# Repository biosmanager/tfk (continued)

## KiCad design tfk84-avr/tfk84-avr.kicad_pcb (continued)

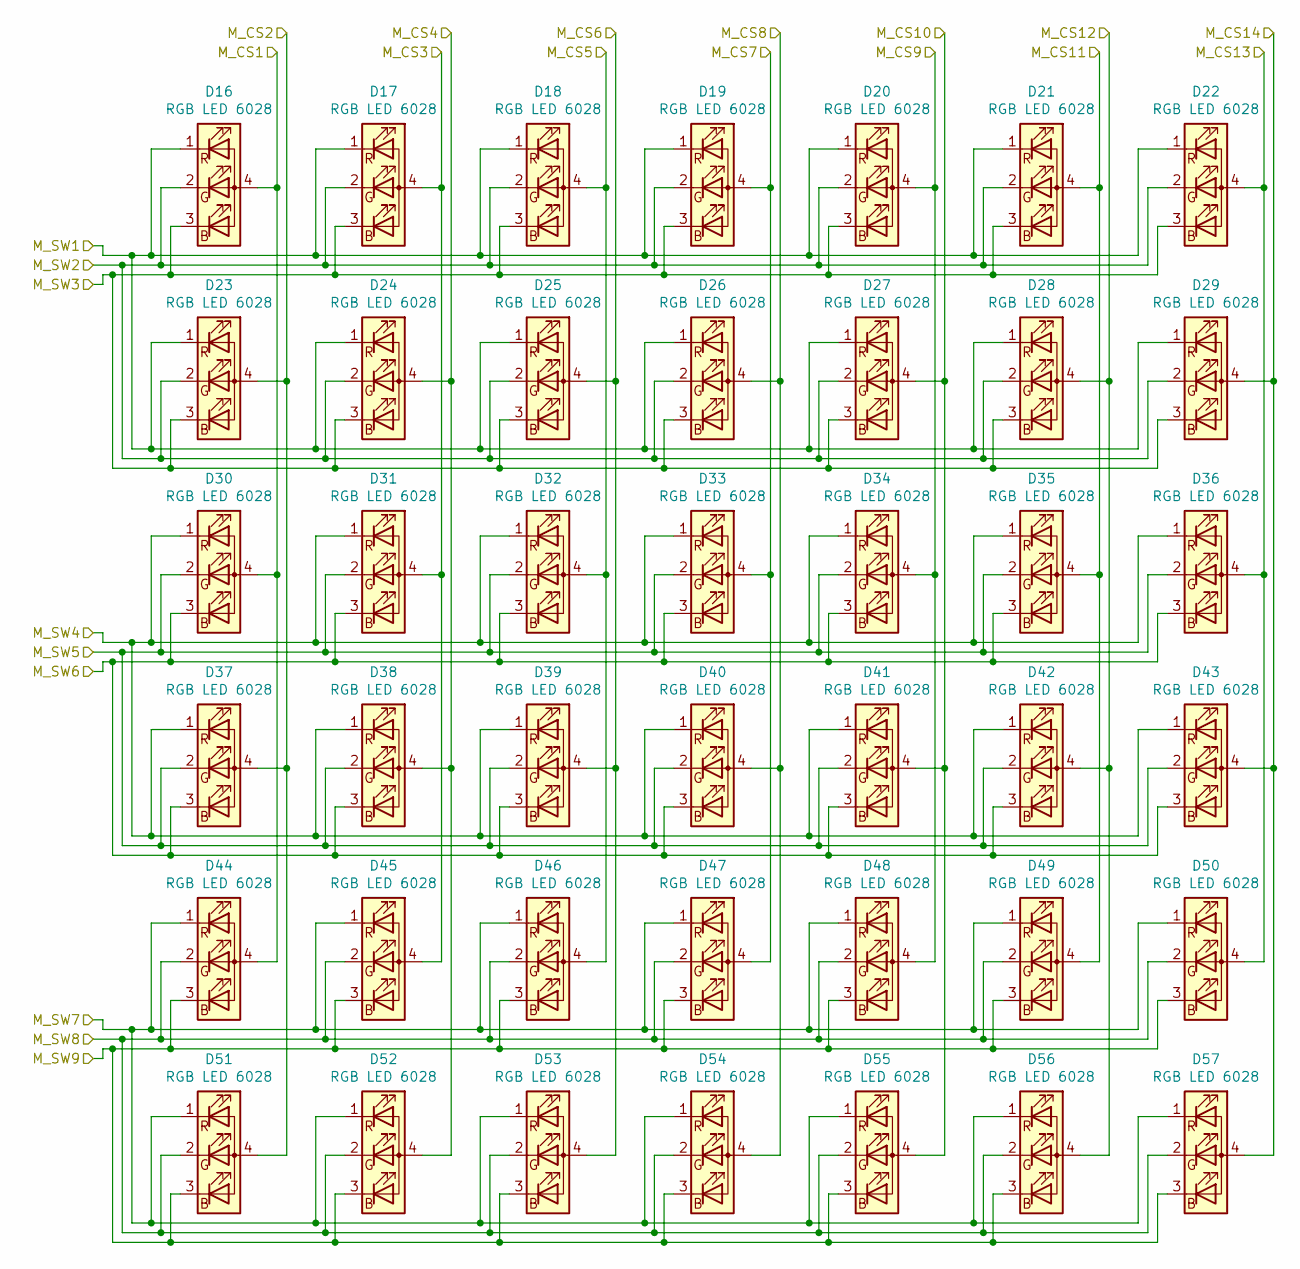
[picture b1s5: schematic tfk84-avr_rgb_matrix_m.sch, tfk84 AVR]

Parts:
D16, D17, D18, D19, D20, D21, D22, D23, D24, D25, D26, D27, D28, D29, D30, D31, D32, D33, D34, D35, D36, D37, D38, D39, D40, D41, D42, D43, D44, D45, D46, D47, D48, D49, D50, D51, D52, D53, D54, D55, D56, D57: RGB LED 6028; RGB-6028

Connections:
/tfk84 RGB Matrix/tfk84 AVR RGB Matrix Master/M_CS1: D16.4 (A), D30.4 (A), D44.4 (A); also elsewhere on the board
/tfk84 RGB Matrix/tfk84 AVR RGB Matrix Master/M_CS2: D23.4 (A), D37.4 (A), D51.4 (A); also elsewhere on the board
/tfk84 RGB Matrix/tfk84 AVR RGB Matrix Master/M_CS3: D17.4 (A), D31.4 (A), D45.4 (A); also elsewhere on the board
/tfk84 RGB Matrix/tfk84 AVR RGB Matrix Master/M_CS4: D24.4 (A), D38.4 (A), D52.4 (A); also elsewhere on the board
/tfk84 RGB Matrix/tfk84 AVR RGB Matrix Master/M_CS5: D18.4 (A), D32.4 (A), D46.4 (A); also elsewhere on the board
/tfk84 RGB Matrix/tfk84 AVR RGB Matrix Master/M_CS6: D25.4 (A), D39.4 (A), D53.4 (A); also elsewhere on the board
/tfk84 RGB Matrix/tfk84 AVR RGB Matrix Master/M_CS7: D19.4 (A), D33.4 (A), D47.4 (A); also elsewhere on the board
/tfk84 RGB Matrix/tfk84 AVR RGB Matrix Master/M_CS8: D26.4 (A), D40.4 (A), D54.4 (A); also elsewhere on the board
/tfk84 RGB Matrix/tfk84 AVR RGB Matrix Master/M_CS9: D20.4 (A), D34.4 (A), D48.4 (A); also elsewhere on the board
/tfk84 RGB Matrix/tfk84 AVR RGB Matrix Master/M_CS10: D27.4 (A), D41.4 (A), D55.4 (A); also elsewhere on the board
/tfk84 RGB Matrix/tfk84 AVR RGB Matrix Master/M_CS11: D21.4 (A), D35.4 (A), D49.4 (A); also elsewhere on the board
/tfk84 RGB Matrix/tfk84 AVR RGB Matrix Master/M_CS12: D28.4 (A), D42.4 (A), D56.4 (A); also elsewhere on the board
/tfk84 RGB Matrix/tfk84 AVR RGB Matrix Master/M_CS13: D22.4 (A), D36.4 (A), D50.4 (A); also elsewhere on the board
/tfk84 RGB Matrix/tfk84 AVR RGB Matrix Master/M_CS14: D29.4 (A), D43.4 (A), D57.4 (A); also elsewhere on the board
/tfk84 RGB Matrix/tfk84 AVR RGB Matrix Master/M_SW1: D16.1 (RK), D17.1 (RK), D18.1 (RK), D19.1 (RK), D20.1 (RK), D21.1 (RK), D22.1 (RK), D23.1 (RK), D24.1 (RK), D25.1 (RK), D26.1 (RK), D27.1 (RK), D28.1 (RK), D29.1 (RK); also elsewhere on the board
/tfk84 RGB Matrix/tfk84 AVR RGB Matrix Master/M_SW2: D16.2 (GK), D17.2 (GK), D18.2 (GK), D19.2 (GK), D20.2 (GK), D21.2 (GK), D22.2 (GK), D23.2 (GK), D24.2 (GK), D25.2 (GK), D26.2 (GK), D27.2 (GK), D28.2 (GK), D29.2 (GK); also elsewhere on the board
/tfk84 RGB Matrix/tfk84 AVR RGB Matrix Master/M_SW3: D16.3 (BK), D17.3 (BK), D18.3 (BK), D19.3 (BK), D20.3 (BK), D21.3 (BK), D22.3 (BK), D23.3 (BK), D24.3 (BK), D25.3 (BK), D26.3 (BK), D27.3 (BK), D28.3 (BK), D29.3 (BK); also elsewhere on the board
/tfk84 RGB Matrix/tfk84 AVR RGB Matrix Master/M_SW4: D30.1 (RK), D31.1 (RK), D32.1 (RK), D33.1 (RK), D34.1 (RK), D35.1 (RK), D36.1 (RK), D37.1 (RK), D38.1 (RK), D39.1 (RK), D40.1 (RK), D41.1 (RK), D42.1 (RK), D43.1 (RK); also elsewhere on the board
/tfk84 RGB Matrix/tfk84 AVR RGB Matrix Master/M_SW5: D30.2 (GK), D31.2 (GK), D32.2 (GK), D33.2 (GK), D34.2 (GK), D35.2 (GK), D36.2 (GK), D37.2 (GK), D38.2 (GK), D39.2 (GK), D40.2 (GK), D41.2 (GK), D42.2 (GK), D43.2 (GK); also elsewhere on the board
/tfk84 RGB Matrix/tfk84 AVR RGB Matrix Master/M_SW6: D30.3 (BK), D31.3 (BK), D32.3 (BK), D33.3 (BK), D34.3 (BK), D35.3 (BK), D36.3 (BK), D37.3 (BK), D38.3 (BK), D39.3 (BK), D40.3 (BK), D41.3 (BK), D42.3 (BK), D43.3 (BK); also elsewhere on the board
/tfk84 RGB Matrix/tfk84 AVR RGB Matrix Master/M_SW7: D44.1 (RK), D45.1 (RK), D46.1 (RK), D47.1 (RK), D48.1 (RK), D49.1 (RK), D50.1 (RK), D51.1 (RK), D52.1 (RK), D53.1 (RK), D54.1 (RK), D55.1 (RK), D56.1 (RK), D57.1 (RK); also elsewhere on the board
/tfk84 RGB Matrix/tfk84 AVR RGB Matrix Master/M_SW8: D44.2 (GK), D45.2 (GK), D46.2 (GK), D47.2 (GK), D48.2 (GK), D49.2 (GK), D50.2 (GK), D51.2 (GK), D52.2 (GK), D53.2 (GK), D54.2 (GK), D55.2 (GK), D56.2 (GK), D57.2 (GK); also elsewhere on the board
/tfk84 RGB Matrix/tfk84 AVR RGB Matrix Master/M_SW9: D44.3 (BK), D45.3 (BK), D46.3 (BK), D47.3 (BK), D48.3 (BK), D49.3 (BK), D50.3 (BK), D51.3 (BK), D52.3 (BK), D53.3 (BK), D54.3 (BK), D55.3 (BK), D56.3 (BK), D57.3 (BK); also elsewhere on the board

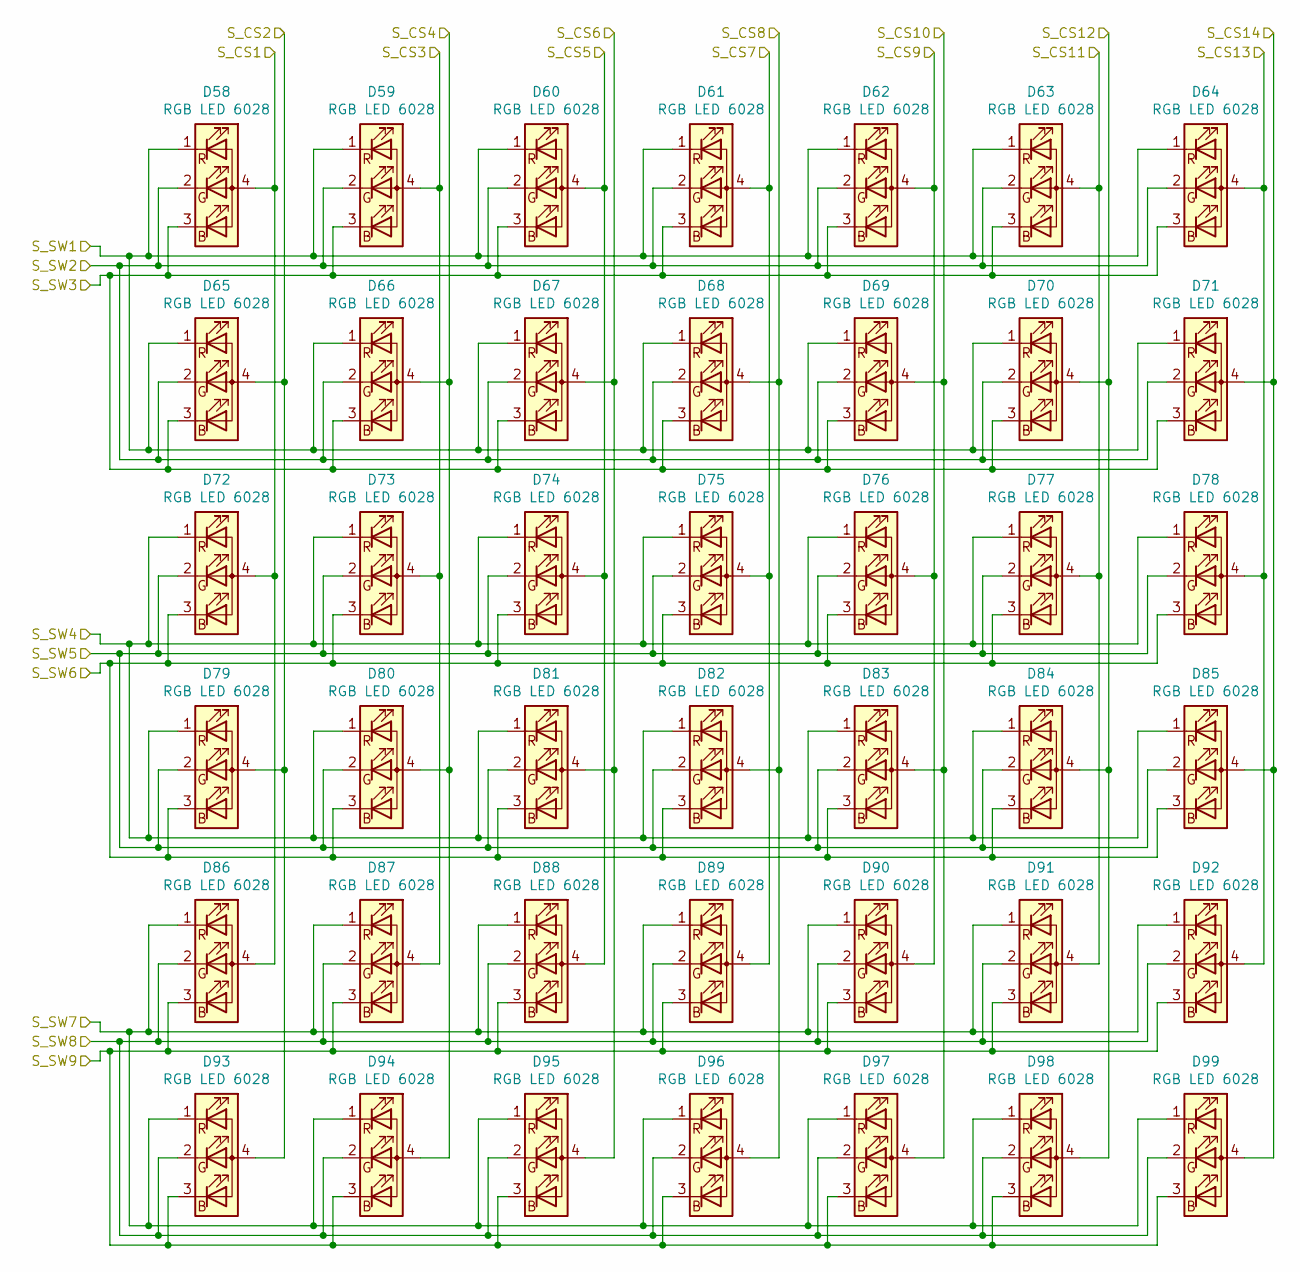
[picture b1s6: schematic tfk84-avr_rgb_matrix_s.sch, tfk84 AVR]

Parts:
D58, D59, D60, D61, D62, D63, D64, D65, D66, D67, D68, D69, D70, D71, D72, D73, D74, D75, D76, D77, D78, D79, D80, D81, D82, D83, D84, D85, D86, D87, D88, D89, D90, D91, D92, D93, D94, D95, D96, D97, D98, D99: RGB LED 6028; RGB-6028

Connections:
/tfk84 RGB Matrix/tfk84 AVR RGB Matrix Slave/S_CS1: D58.4 (A), D72.4 (A), D86.4 (A); also elsewhere on the board
/tfk84 RGB Matrix/tfk84 AVR RGB Matrix Slave/S_CS2: D65.4 (A), D79.4 (A), D93.4 (A); also elsewhere on the board
/tfk84 RGB Matrix/tfk84 AVR RGB Matrix Slave/S_CS3: D59.4 (A), D73.4 (A), D87.4 (A); also elsewhere on the board
/tfk84 RGB Matrix/tfk84 AVR RGB Matrix Slave/S_CS4: D66.4 (A), D80.4 (A), D94.4 (A); also elsewhere on the board
/tfk84 RGB Matrix/tfk84 AVR RGB Matrix Slave/S_CS5: D60.4 (A), D74.4 (A), D88.4 (A); also elsewhere on the board
/tfk84 RGB Matrix/tfk84 AVR RGB Matrix Slave/S_CS6: D67.4 (A), D81.4 (A), D95.4 (A); also elsewhere on the board
/tfk84 RGB Matrix/tfk84 AVR RGB Matrix Slave/S_CS7: D61.4 (A), D75.4 (A), D89.4 (A); also elsewhere on the board
/tfk84 RGB Matrix/tfk84 AVR RGB Matrix Slave/S_CS8: D68.4 (A), D82.4 (A), D96.4 (A); also elsewhere on the board
/tfk84 RGB Matrix/tfk84 AVR RGB Matrix Slave/S_CS9: D62.4 (A), D76.4 (A), D90.4 (A); also elsewhere on the board
/tfk84 RGB Matrix/tfk84 AVR RGB Matrix Slave/S_CS10: D69.4 (A), D83.4 (A), D97.4 (A); also elsewhere on the board
/tfk84 RGB Matrix/tfk84 AVR RGB Matrix Slave/S_CS11: D63.4 (A), D77.4 (A), D91.4 (A); also elsewhere on the board
/tfk84 RGB Matrix/tfk84 AVR RGB Matrix Slave/S_CS12: D70.4 (A), D84.4 (A), D98.4 (A); also elsewhere on the board
/tfk84 RGB Matrix/tfk84 AVR RGB Matrix Slave/S_CS13: D64.4 (A), D78.4 (A), D92.4 (A); also elsewhere on the board
/tfk84 RGB Matrix/tfk84 AVR RGB Matrix Slave/S_CS14: D71.4 (A), D85.4 (A), D99.4 (A); also elsewhere on the board
/tfk84 RGB Matrix/tfk84 AVR RGB Matrix Slave/S_SW1: D58.1 (RK), D59.1 (RK), D60.1 (RK), D61.1 (RK), D62.1 (RK), D63.1 (RK), D64.1 (RK), D65.1 (RK), D66.1 (RK), D67.1 (RK), D68.1 (RK), D69.1 (RK), D70.1 (RK), D71.1 (RK); also elsewhere on the board
/tfk84 RGB Matrix/tfk84 AVR RGB Matrix Slave/S_SW2: D58.2 (GK), D59.2 (GK), D60.2 (GK), D61.2 (GK), D62.2 (GK), D63.2 (GK), D64.2 (GK), D65.2 (GK), D66.2 (GK), D67.2 (GK), D68.2 (GK), D69.2 (GK), D70.2 (GK), D71.2 (GK); also elsewhere on the board
/tfk84 RGB Matrix/tfk84 AVR RGB Matrix Slave/S_SW3: D58.3 (BK), D59.3 (BK), D60.3 (BK), D61.3 (BK), D62.3 (BK), D63.3 (BK), D64.3 (BK), D65.3 (BK), D66.3 (BK), D67.3 (BK), D68.3 (BK), D69.3 (BK), D70.3 (BK), D71.3 (BK); also elsewhere on the board
/tfk84 RGB Matrix/tfk84 AVR RGB Matrix Slave/S_SW4: D72.1 (RK), D73.1 (RK), D74.1 (RK), D75.1 (RK), D76.1 (RK), D77.1 (RK), D78.1 (RK), D79.1 (RK), D80.1 (RK), D81.1 (RK), D82.1 (RK), D83.1 (RK), D84.1 (RK), D85.1 (RK); also elsewhere on the board
/tfk84 RGB Matrix/tfk84 AVR RGB Matrix Slave/S_SW5: D72.2 (GK), D73.2 (GK), D74.2 (GK), D75.2 (GK), D76.2 (GK), D77.2 (GK), D78.2 (GK), D79.2 (GK), D80.2 (GK), D81.2 (GK), D82.2 (GK), D83.2 (GK), D84.2 (GK), D85.2 (GK); also elsewhere on the board
/tfk84 RGB Matrix/tfk84 AVR RGB Matrix Slave/S_SW6: D72.3 (BK), D73.3 (BK), D74.3 (BK), D75.3 (BK), D76.3 (BK), D77.3 (BK), D78.3 (BK), D79.3 (BK), D80.3 (BK), D81.3 (BK), D82.3 (BK), D83.3 (BK), D84.3 (BK), D85.3 (BK); also elsewhere on the board
/tfk84 RGB Matrix/tfk84 AVR RGB Matrix Slave/S_SW7: D86.1 (RK), D87.1 (RK), D88.1 (RK), D89.1 (RK), D90.1 (RK), D91.1 (RK), D92.1 (RK), D93.1 (RK), D94.1 (RK), D95.1 (RK), D96.1 (RK), D97.1 (RK), D98.1 (RK), D99.1 (RK); also elsewhere on the board
/tfk84 RGB Matrix/tfk84 AVR RGB Matrix Slave/S_SW8: D86.2 (GK), D87.2 (GK), D88.2 (GK), D89.2 (GK), D90.2 (GK), D91.2 (GK), D92.2 (GK), D93.2 (GK), D94.2 (GK), D95.2 (GK), D96.2 (GK), D97.2 (GK), D98.2 (GK), D99.2 (GK); also elsewhere on the board
/tfk84 RGB Matrix/tfk84 AVR RGB Matrix Slave/S_SW9: D86.3 (BK), D87.3 (BK), D88.3 (BK), D89.3 (BK), D90.3 (BK), D91.3 (BK), D92.3 (BK), D93.3 (BK), D94.3 (BK), D95.3 (BK), D96.3 (BK), D97.3 (BK), D98.3 (BK), D99.3 (BK); also elsewhere on the board

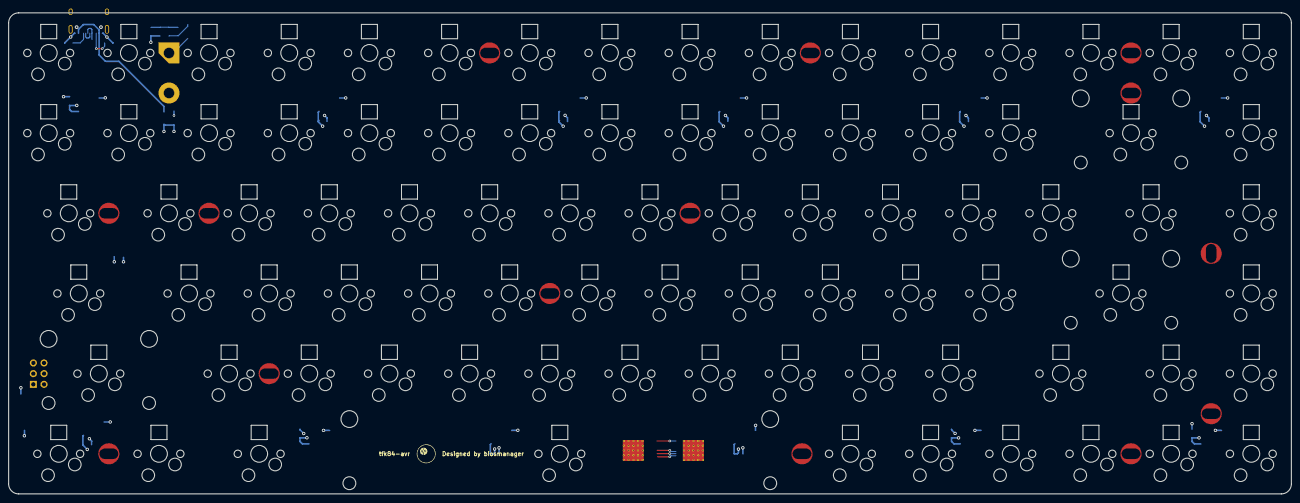
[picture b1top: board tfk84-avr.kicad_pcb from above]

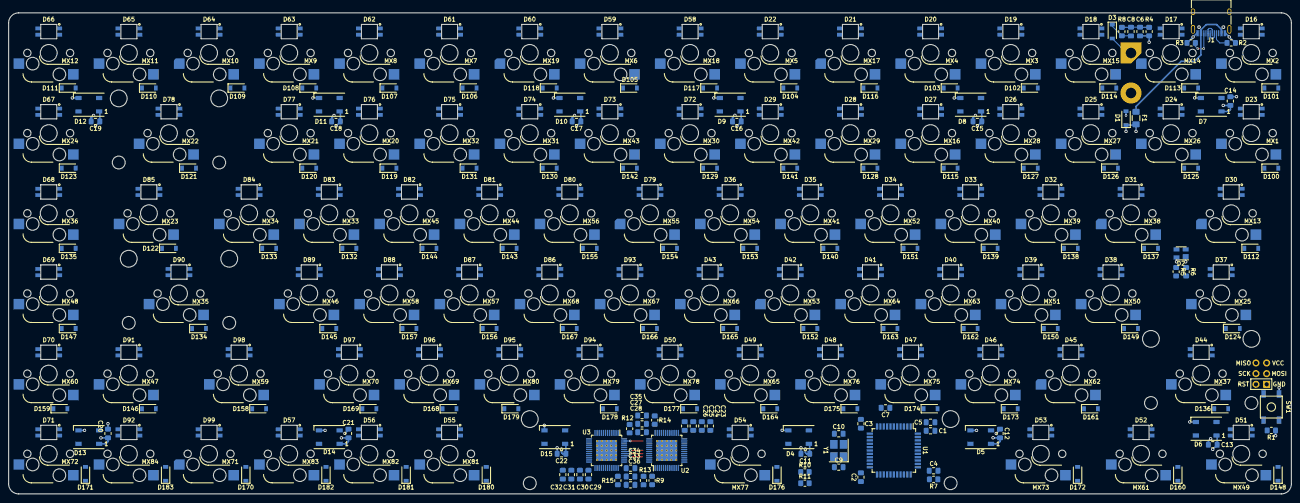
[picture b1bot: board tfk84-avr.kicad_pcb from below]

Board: 4 copper layers, 304.8 x 114.3 mm, 346 parts (242 on the bottom side), 189 nets.

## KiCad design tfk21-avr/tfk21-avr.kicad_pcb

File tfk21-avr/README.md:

# tfk21-avr

21 key hot-swap RGB numpad with extra row on top. Uses Microchip ATmega32U4-AU microcontroller. 
All footprints should be suitable for hand soldering.

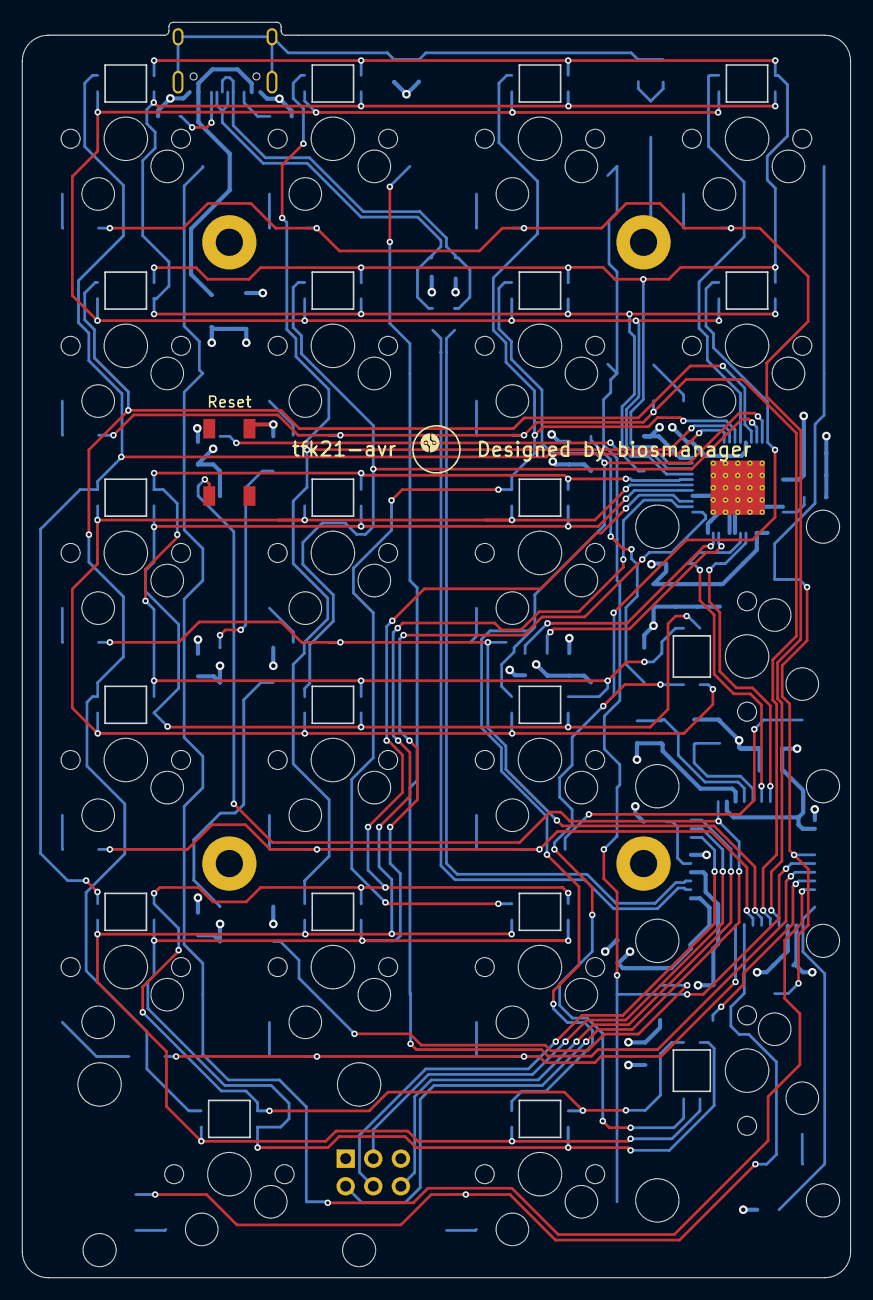
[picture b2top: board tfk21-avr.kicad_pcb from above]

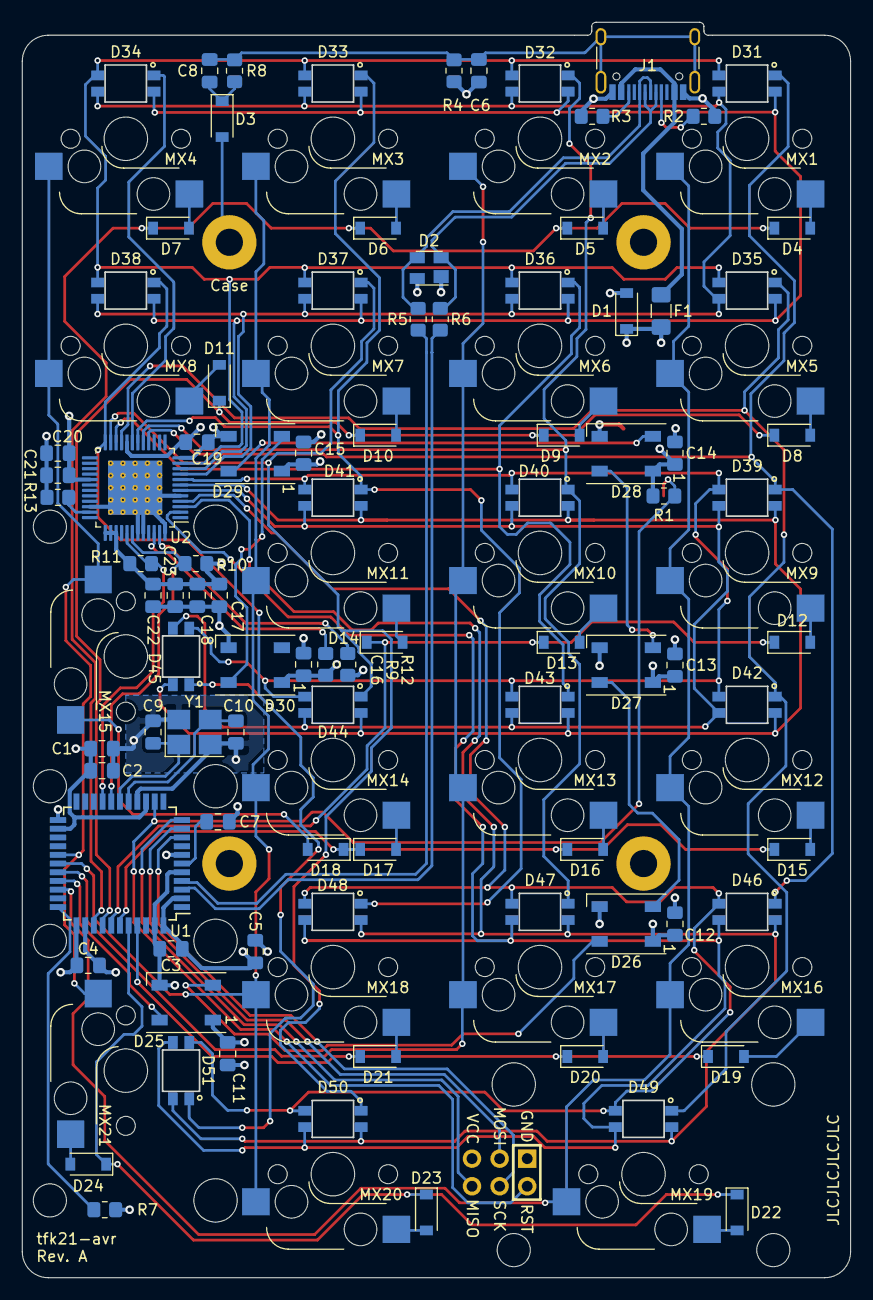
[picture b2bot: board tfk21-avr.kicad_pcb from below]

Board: 4 copper layers, 76.2 x 115.4 mm, 123 parts (93 on the bottom side), 79 nets.

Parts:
C1, C2, C3, C4: 0.1u; C_0805_2012Metric_Pad1.18x1.45mm_HandSolder
C5: 10u; C_0805_2012Metric_Pad1.18x1.45mm_HandSolder
C6, C8: 4.7n; C_0805_2012Metric_Pad1.18x1.45mm_HandSolder
C7: 1u; C_0805_2012Metric_Pad1.18x1.45mm_HandSolder
C9, C10: 22p; C_0805_2012Metric_Pad1.18x1.45mm_HandSolder
C11, C12, C13, C14, C15, C16, C19, C21, C23: 100n; C_0805_2012Metric_Pad1.18x1.45mm_HandSolder
C17, C18, C20, C22: 470n; C_0805_2012Metric_Pad1.18x1.45mm_HandSolder
D1: 6V; D_SOD-123
D2: PRTR5V0U2X; SOT-143
D3: Case ESD; D_SOD-123
D4, D5, D6, D7, D8, D9, D10, D11, D12, D13, D14, D15, D16, D17, D18, D19, D20, D21, D22, D23, D24: Switch diode; D_SOD-123
D25, D26, D27, D28, D29, D30: WS2812B; LED_WS2812B_PLCC4_5.0x5.0mm_P3.2mm
D31, D32, D33, D34, D35, D36, D37, D38, D39, D40, D41, D42, D43, D44, D45, D46, D47, D48, D49, D50, D51: LED_RGBA; RGB-6028
F1: 500mA; Fuse_1206_3216Metric_Pad1.42x1.75mm_HandSolder
G1: LOGO; biosmanager_pcb
H1, H3, H4: MountingHole; MountingHole_2.5mm_Pad
H2: Case; MountingHole_2.5mm_Pad
H5, H6, H7: Stabilizer; Stabilizer_Cherry_MX_2u_CrtYd
J1: USB_C_Receptacle_USB2.0; USB_C_Receptacle_HRO_TYPE-C-31-M-12
J2: AVR-ISP-6; Reset_Pretty-Mask
MX1, MX2, MX3, MX4, MX5, MX6, MX7, MX8, MX9, MX10, MX11, MX12, MX13, MX14, MX16, MX17, MX18, MX20: MX-NoLED; SW_Hotswap_Kailh_1.00u_NoFrontSilk
MX15, MX19, MX21: MX-NoLED; SW_Hotswap_Kailh_2.00u_NoFrontSilk
R1, R7: 10k; R_0805_2012Metric_Pad1.20x1.40mm_HandSolder
R2, R3: 5.1k; R_0805_2012Metric_Pad1.20x1.40mm_HandSolder
R4, R8: 1M; R_0805_2012Metric_Pad1.20x1.40mm_HandSolder
R5, R6: 22; R_0805_2012Metric_Pad1.20x1.40mm_HandSolder
R9, R12: 100k; R_0805_2012Metric_Pad1.20x1.40mm_HandSolder
R10, R11: 2k; R_0805_2012Metric_Pad1.20x1.40mm_HandSolder
R13: 20k; R_0805_2012Metric_Pad1.20x1.40mm_HandSolder
SW1: Reset; SKQG-1155865
U1: ATmega32U4-AU; TQFP-44_10x10mm_P0.8mm
U2: IS31FL3733B-TQLS4-TR; TQFP-48-1EP_7x7mm_P0.5mm_EP5x5mm_ThermalVias
Y1: 16MHz; Crystal_SMD_3225-4Pin_3.2x2.5mm_HandSoldering

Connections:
+5V: C1.1, C2.1, C3.1, C4.1, C5.1, C11.1, C12.1, C13.1, C14.1, C15.1, C16.1, C17.1, C18.1, C19.1, C20.1, C21.1, C22.1, C23.2, D1.1, D2.4, D25.1, D26.1, D27.1, D28.1, D29.1, D30.1, F1.1, J2.2, R1.1, R9.1, R10.1, R11.1, U1.2, U1.7, U1.14, U1.24, U1.34, U1.44, U2.20, U2.29, U2.37, U2.38, U2.39
/COL_0: MX1.1, MX5.1, MX9.1, MX12.1, MX16.1, MX19.1, U1.31
/COL_1: MX2.1, MX6.1, MX10.1, MX13.1, MX17.1, U1.29
/COL_2: MX3.1, MX7.1, MX11.1, MX14.1, MX18.1, MX20.1, U1.28
/COL_3: MX4.1, MX8.1, MX15.1, MX21.1, U1.27
/IN_USB_D+: D2.3, J1.A6, J1.B6, R5.1
/IN_USB_D-: D2.2, J1.A7, J1.B7, R6.1
/MCU_USB_D+: R5.2, U1.4
/MCU_USB_D-: R6.2, U1.3
/MISO: J2.1, U1.11
/MOSI: J2.4, U1.10
/RESET: J2.5, R1.2, SW1.2, U1.13
/RGB_LIGHT: D25.4, U1.30
/RGB_MATRIX_SCL: R10.2, U1.18, U2.42
/RGB_MATRIX_SDA: R11.2, U1.19, U2.41
/ROW_0: D4.1, D5.1, D6.1, D7.1, U1.36
/ROW_1: D8.1, D9.1, D10.1, D11.1, U1.37
/ROW_2: D12.1, D13.1, D14.1, U1.38
/ROW_3: D15.1, D16.1, D17.1, D18.1, U1.39
/ROW_4: D19.1, D20.1, D21.1, U1.41
/ROW_5: D22.1, D23.1, D24.1, U1.40
/SCK: J2.3, U1.9
/SHIELD: C6.1, C8.2, J1.S1, R4.1, R8.2
/XTAL1: C9.2, U1.17, Y1.1
/XTAL2: C10.1, U1.16, Y1.3
/tfk21 RGB Matrix/CS1: D31.4, D39.4, D46.4, U2.16
/tfk21 RGB Matrix/CS2: D32.4, D40.4, D47.4, U2.17
/tfk21 RGB Matrix/CS3: D33.4, D41.4, D48.4, U2.18
/tfk21 RGB Matrix/CS4: D34.4, U2.19
/tfk21 RGB Matrix/CS5: D35.4, D42.4, D49.4, U2.21
/tfk21 RGB Matrix/CS6: D36.4, D43.4, U2.22
/tfk21 RGB Matrix/CS7: D37.4, D44.4, D50.4, U2.23
/tfk21 RGB Matrix/CS8: D38.4, D45.4, D51.4, U2.24
/tfk21 RGB Matrix/SW1: D46.3, D47.3, D48.3, D49.3, D50.3, D51.3, U2.2
/tfk21 RGB Matrix/SW2: D46.1, D47.1, D48.1, D49.1, D50.1, D51.1, U2.3
/tfk21 RGB Matrix/SW3: D46.2, D47.2, D48.2, D49.2, D50.2, D51.2, U2.4
/tfk21 RGB Matrix/SW4: D39.3, D40.3, D41.3, D42.3, D43.3, D44.3, D45.3, U2.6
/tfk21 RGB Matrix/SW5: D39.1, D40.1, D41.1, D42.1, D43.1, D44.1, D45.1, U2.7
/tfk21 RGB Matrix/SW6: D39.2, D40.2, D41.2, D42.2, D43.2, D44.2, D45.2, U2.8
/tfk21 RGB Matrix/SW7: D31.3, D32.3, D33.3, D34.3, D35.3, D36.3, D37.3, D38.3, U2.9
/tfk21 RGB Matrix/SW8: D31.1, D32.1, D33.1, D34.1, D35.1, D36.1, D37.1, D38.1, U2.10
/tfk21 RGB Matrix/SW9: D31.2, D32.2, D33.2, D34.2, D35.2, D36.2, D37.2, D38.2, U2.11
GND: C1.2, C2.2, C3.2, C4.2, C5.2, C6.2, C7.2, C9.1, C10.2, C11.2, C12.2, C13.2, C14.2, C15.2, C16.2, C17.2, C18.2, C19.2, C20.2, C21.2, C22.2, C23.1, D1.2, D2.1, D25.3, D26.3, D27.3, D28.3, D29.3, D30.3, J1.A1, J1.A12, J1.B1, J1.B12, J2.6, R2.1, R3.2, R4.2, R7.1, R12.1, R13.1, SW1.1, U1.5, U1.15, U1.23, U1.35, U1.43, U2.5, U2.12, U2.34, U2.43, U2.44, U2.48, U2.49, Y1.2, Y1.4
unnamed: C7.1, U1.6
unnamed: C8.1, D3.1, R8.1
unnamed: D3.2, H2.1
unnamed: D4.2, MX1.2
unnamed: D5.2, MX2.2
unnamed: D6.2, MX3.2
unnamed: D7.2, MX4.2
unnamed: D8.2, MX5.2
unnamed: D9.2, MX6.2
unnamed: D10.2, MX7.2
unnamed: D11.2, MX8.2
unnamed: D12.2, MX9.2
unnamed: D13.2, MX10.2
unnamed: D14.2, MX11.2
unnamed: D15.2, MX12.2
unnamed: D16.2, MX13.2
unnamed: D17.2, MX14.2
unnamed: D18.2, MX15.2
unnamed: D19.2, MX16.2
unnamed: D20.2, MX17.2
unnamed: D21.2, MX18.2
unnamed: D22.2, MX19.2
unnamed: D23.2, MX20.2
unnamed: D24.2, MX21.2
unnamed: D25.2, D26.4
unnamed: D26.2, D27.4
unnamed: D27.2, D28.4
unnamed: D28.2, D29.4
unnamed: D29.2, D30.4
unnamed: J1.A5, R2.2
unnamed: J1.B5, R3.1
unnamed: R7.2, U1.33
unnamed: R9.2, U2.46
unnamed: R12.2, U2.47
unnamed: R13.2, U2.35
VBUS: F1.2, J1.A4, J1.A9, J1.B4, J1.B9

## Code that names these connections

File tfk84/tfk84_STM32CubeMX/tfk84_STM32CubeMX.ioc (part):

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PB13.GPIOParameters=GPIO_Label
PA6.Mode=Full_Duplex_Master
PC7.GPIOParameters=GPIO_Label
Mcu.UserName=STM32F303RCTx
PC10.Signal=GPIO_Output
PC12.Signal=GPIO_Output
PB14.GPIO_Label=ROW_5
RCC.SYSCLKSourceVirtual=RCC_SYSCLKSOURCE_PLLCLK
PC0.GPIOParameters=GPIO_Label
PC0.GPIO_Label=COL_0
PC6.GPIO_Label=COL_6
PA11.Mode=Device
RCC.HSEPLLFreq_Value=8000000
PC13.GPIO_Label=COL_13
PB13.GPIO_Label=ROW_4
PB11.Signal=GPIO_Input
PB13.Signal=GPIO_Input
PB15.Signal=GPIO_Input
PA12.Signal=USB_DP
PC1.GPIOParameters=GPIO_Label
PB6.Signal=I2C1_SCL
PC7.Signal=GPIO_Output
PB6.Mode=I2C
PC3.Signal=GPIO_Output
RCC.HSE_VALUE=8000000
PB3.Mode=Trace_Asynchronous_SW
PB12.GPIO_Label=ROW_3
PC4.GPIO_Label=COL_4
PA14.Mode=Trace_Asynchronous_SW
PC11.GPIO_Label=COL_11
PB7.Signal=I2C1_SDA
PC14-OSC32_IN.GPIOParameters=GPIO_Label
PC8.GPIOParameters=GPIO_Label
Mcu.Package=LQFP64
PB9.Signal=GPIO_Input
PA6.Signal=SPI1_MISO
PA10.Signal=I2C2_SDA
PB14.GPIOParameters=GPIO_Label
PC14-OSC32_IN.GPIO_Label=COL_14
PC5.Signal=GPIO_Output
PB10.GPIOParameters=GPIO_Label
PF1-OSC_OUT.Mode=HSE-External-Oscillator
PC2.GPIO_Label=COL_2
PC4.GPIOParameters=GPIO_Label
PF1-OSC_OUT.Signal=RCC_OSC_OUT
PA5.Mode=Full_Duplex_Master
PA7.Mode=Full_Duplex_Master
PB9.GPIO_Label=ROW_0
PA10.Mode=I2C
PC10.GPIO_Label=COL_10
PC9.GPIO_Label=COL_9
PC11.Signal=GPIO_Output
PC13.Signal=GPIO_Output
PC8.Signal=GPIO_Output
PC2.Signal=GPIO_Output
PC4.Signal=GPIO_Output
PC6.Signal=GPIO_Output
PB11.GPIO_Label=ROW_2
PC0.Signal=GPIO_Output
PC14-OSC32_IN.Signal=GPIO_Output
PC11.GPIOParameters=GPIO_Label
PB9.GPIOParameters=GPIO_Label
PC3.GPIOParameters=GPIO_Label
PC8.GPIO_Label=COL_8
PC12.GPIOParameters=GPIO_Label
PA13.Signal=SYS_JTMS-SWDIO
PA9.Mode=I2C
PB10.GPIO_Label=ROW_1
PC5.GPIOParameters=GPIO_Label
PA9.Signal=I2C2_SCL
PB11.GPIOParameters=GPIO_Label
PF0-OSC_IN.Mode=HSE-External-Oscillator
PB10.Signal=GPIO_Input
PB14.Signal=GPIO_Input
PA5.Signal=SPI1_SCK
board=custom
PB15.GPIO_Label=ROW_6
PC13.GPIOParameters=GPIO_Label
PC2.GPIOParameters=GPIO_Label
PC1.GPIO_Label=COL_1
PC10.GPIOParameters=GPIO_Label
PB15.GPIOParameters=GPIO_Label
PA13.Mode=Trace_Asynchronous_SW
PC9.GPIOParameters=GPIO_Label
Mcu.Name=STM32F303R(B-C)Tx
PC7.GPIO_Label=COL_7
PB3.Signal=SYS_JTDO-TRACESWO
RCC.SYSCLKFreq_VALUE=48000000
PA12.Mode=Device
PC5.GPIO_Label=COL_5
PC12.GPIO_Label=COL_12
PB7.Mode=I2C
PA11.Signal=USB_DM
PA14.Signal=SYS_JTCK-SWCLK
PC6.GPIOParameters=GPIO_Label
PC3.GPIO_Label=COL_3
PC9.Signal=GPIO_Output
PF0-OSC_IN.Signal=RCC_OSC_IN
PC1.Signal=GPIO_Output
PB12.GPIOParameters=GPIO_Label
PB12.Signal=GPIO_Input
PA7.Signal=SPI1_MOSI

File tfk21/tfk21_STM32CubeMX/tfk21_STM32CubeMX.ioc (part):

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PA6.GPIOParameters=GPIO_Label
PB13.GPIOParameters=GPIO_Label
Mcu.UserName=STM32F072CBTx
PB10.Mode=I2C
PB14.GPIO_Label=COL_2
PA11.Mode=Device
PA3.GPIOParameters=GPIO_Label
PA6.GPIO_Label=ROW_3
PB0.GPIO_Label=ROW_5
PB13.GPIO_Label=COL_1
PB11.Signal=I2C2_SDA
PB13.Signal=GPIO_Output
PB15.Signal=GPIO_Output
RCC.SYSCLKSource=RCC_SYSCLKSOURCE_HSI48
PA13.Signal=SYS_SWDIO
PA12.Signal=USB_DP
PB11.Mode=I2C
PB9.Mode=I2C
PB10.Signal=I2C2_SCL
PB14.Signal=GPIO_Output
PA5.Signal=GPIO_Input
PB3.Mode=Full_Duplex_Master
board=custom
PB12.GPIO_Label=COL_0
PB0.GPIOParameters=GPIO_Label
PB4.Mode=Full_Duplex_Master
PB15.GPIO_Label=COL_3
PA14.Mode=Serial_Wire
PB5.Mode=Full_Duplex_Master
PA4.GPIOParameters=GPIO_Label
PB15.GPIOParameters=GPIO_Label
PA13.Mode=Serial_Wire
Mcu.Name=STM32F072C(8-B)Tx
PB3.Signal=SPI1_SCK
PA4.Signal=GPIO_Input
RCC.SYSCLKFreq_VALUE=48000000
Mcu.Package=LQFP48
PB5.Signal=SPI1_MOSI
PB9.Signal=I2C1_SDA
PA6.Signal=GPIO_Input
PA7.GPIO_Label=ROW_4
PA12.Mode=Device
PA5.GPIO_Label=ROW_2
PA11.Signal=USB_DM
PA14.Signal=SYS_SWCLK
PA5.GPIOParameters=GPIO_Label
PB14.GPIOParameters=GPIO_Label
PB8.Mode=I2C
PB8.Signal=I2C1_SCL
PB0.Signal=GPIO_Input
PA4.GPIO_Label=ROW_1
PA7.GPIOParameters=GPIO_Label
PB12.GPIOParameters=GPIO_Label
PB12.Signal=GPIO_Output
PB4.Signal=SPI1_MISO
PA3.GPIO_Label=ROW_0
PA3.Signal=GPIO_Input
PA7.Signal=GPIO_Input

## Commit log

2021-01-10 Initialize tfk75 project
2021-01-16 Add MCU with decoupling caps and linear regulator
2021-01-27 Add MX/Alps hybrid library
2021-01-29 Add key matrix schematic
2021-01-31 Begin key matrix
2021-01-31 Finish key matrix, start reset circuit
2021-02-01 Begin RGB matrix
2021-02-02 Begin tfk20
2021-02-04 Continue on tfk20
2021-02-07 RGB LED driver
2021-02-08 Change caps layout
2021-02-18 Change MCU, add another row, add reset button
2021-03-01 Implement sophisticated USB-C protection
2021-03-05 Add STL11N3LLH6 footprint
2021-03-14 Fix project
2021-06-04 Implement tfk20 AVR schematic
2021-06-04 Set AVR suffix consistently
2021-06-05 Add mounting holes
2021-06-05 Remove alternative switch positions
2021-06-06 Add ISP header
2021-06-06 Add various libraries as submodules
2021-06-06 Assign some footprints
2021-06-06 Remove alternative LEDs
2021-06-06 Assigned remaining footprints
2021-06-06 Begin PCB
2021-06-07 Place all footprints on PCB
2021-06-07 Fix clearance and courtyard issues
2021-06-08 Begin north-facing LED layout
2021-06-09 Finish north-facing LED footprint layout
2021-06-10 Continue routing
2021-06-12 Finish routing
2021-06-12 Update keyswitch library
2021-06-12 Add dimensions
2021-06-12 Tweak some things
2021-06-12 Add signature
2021-06-14 Start new 4 layer layout
2021-06-14 Route VBUS
2021-06-15 Route PWR and GND
2021-06-15 Route columns
2021-06-16 Tweak some routes
2021-06-17 Fix silkscreen
2021-06-17 Place OVP diode after fuse
2021-06-17 Clean up
2021-06-17 Tweak silk screen
2021-06-17 Rename tfk20 to tfk21
2021-06-17 Rename tfk20 and tfk75
2021-06-18 Add 3D models
2021-06-19 Fix absolute paths
2021-06-19 Add more dimensions
2021-06-19 Tweak position of C5 to allow more space for stabilizer
2021-06-20 Fix LED driver resistors and mounting hole pads
2021-06-20 Use newer revision of LED driver
2021-06-24 Add dimension
2021-06-24 Add location of JLCPCB order number
2021-06-24 Set plot settings for JLCPCB
2021-06-24 Hide silkscreen graphic lines
2021-06-24 Plot values in Gerbers
2021-06-25 Tweak component values
2021-06-25 Add Gerber files, BOM and schematic PDF
2021-06-27 Expose LED thermal pad on front for easier soldering
2021-06-27 Change key matrix to 12x7
2021-06-27 Continue schematic
2021-06-27 Begin tfk84-avr schematic
2021-06-27 Add RGB matrices
2021-06-27 Begin placing mounting holes
2021-06-27 Continue layout
2021-06-28 Add mounting holes for XD84 and KBD75V2 cases
2021-06-28 Tweak holes
2021-06-28 Place switch diodes
2021-07-03 Layout backlight LEDs
2021-07-03 Place all components on board
2021-07-03 Fix DRC errors
2021-07-03 Layout switch diodes
2021-07-25 Minor tweaks
